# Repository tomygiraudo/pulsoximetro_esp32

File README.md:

# Pulsoximetro portátil WI-FI

Diseño open-source de un pulsioxímetro doméstico portátil con conexión WI-FI para la materia de instrumentación Biomédica, realizado con un ESP32-C3 Super mini, un sensor de Fotoplestimografía (PPG) MAX30102, un circuito de carga y control de batería, una baterpia de 3.7 V y 230 mAh y una pantalla TFT 128x128 px con controlador STF775S.
<div align="center"> 

</div>

Detalles:

- **Ciclo de medición:** el dashboard espera en "Listo para medir" hasta que el
  ESP32 manda el paquete de inicio (se presionó el botón de medición); recién
  entonces aparecen las lecturas, el cronómetro y la traza PPG. Al terminar la
  medición el dashboard deja 2 minutos el resultado final (SpO₂, BPM y la señal)
  antes de volver a "Listo para medir"; si se empieza otra medición antes, la
  reemplaza.
- **Firmware** El firmware se encuentra en firmware/pulsox, tiene integrado todo lo hecho en los distintos tests de las otras carpetas.
- **Credenciales** Para que el pulsoxímetro se conecte a la aplicación y a la base de datos, se debe clonar el codigo de la base de datos y alojarlo en un proyecto firebase local. Por ultimo crear un archivo .env con las credenciales de la red wifi y las API's correspondientes para establecer la conexión con la base de datos.

## Procesamiento de Señal y diseño de filtros en Python
https://colab.research.google.com/drive/18P-XyyEuqM189sJWGMnf9TlH9UD-HeR_?usp=sharing 

Links útiles del fabricante del MAX30102: 
https://www.analog.com/en/resources/reference-designs/maxrefdes117.html
https://www.analog.com/en/resources/technical-articles/how-to-design-a-better-pulse-oximeter.html 
https://www.analog.com/en/resources/technical-articles/guidelines-for-spo2-measurement--maxim-integrated.html
https://www.scielo.cl/scielo.php?script=sci_arttext&pid=S0717-73482010000100010

## Hardware
El esquemático del pulsioxímetro y todos sus componentes necesarios se detallan en PCB/Esquematico_V2.pdf/. Los archivos de diseño de la PCB se encuentran dentro de la misma carpeta. 

## Impresión de Carcasa
Los archivos STL para la impresión de la carcasa se encuentran en Carcasa/. Las partes fueron impresas en PETG para una mayor resistencia. 
**Parámetros de Impresión**
-  Altura de capa: 0,16 mm
-  Perímetros: 5 * 0,4 mm
-  Relleno: 50% o superior

## Telemetría del ESP32

El ESP32-C3 envía cada medición por **HTTPS (REST) a Firebase Realtime Database**. La web app la muestra en vivo y la guarda en el historial.

- **Conexión:** al presionar el botón, el ESP32 se conecta al WiFi, inicia sesión en Firebase y mantiene una sola conexión TLS abierta durante la medición.
- **En vivo (1 Hz):** cada segundo reemplaza `devices/<id>/live` con SpO₂, BPM, calidad de señal, estado del dedo y la traza PPG (50 muestras/s). Al terminar, borra `live`.
- **Historial:** una medición válida (45–60 s) guarda una única lectura final en `sessions/<sid>`. El valor es la mediana de los últimos 20 s válidos. Si la medición se descarta (dedo retirado o señal errática), la sesión se borra.
- **Credenciales:** WiFi, API key y usuario del dispositivo van en `firmware/pulsox/include/secrets.h`. El archivo se crea a partir de `secrets.h.example` y no se sube al repo.

Detalle de nodos, llamadas REST y reglas de seguridad en [`PROTOCOL.md`](PROTOCOL.md). Firmware en [`firmware/pulsox`](firmware/pulsox).

## Sistema de diseño y tipografías para pantalla y app web 

Ver [`design-system/pulsox-esp32/`](design-system/pulsox-esp32/): paleta,
tipografía, formas y especificación de componentes (gauge de SpO2, tarjeta de
frecuencia cardíaca, traza PPG, barra de navegación, historial) usados por la
web app.
<div align="center">
   
</div>
<div align="center">
                        
  </div>

## Próximos pasos

- Comparar mediciones con un patrón y realizar una calibración o informe de resultados.

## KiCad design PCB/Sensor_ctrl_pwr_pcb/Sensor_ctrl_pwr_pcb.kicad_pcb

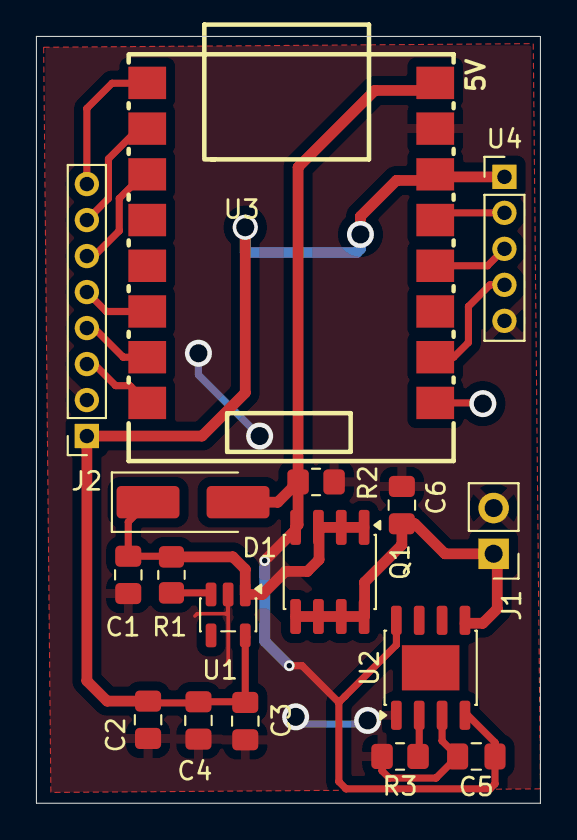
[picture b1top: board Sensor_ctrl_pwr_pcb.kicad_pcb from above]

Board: 2 copper layers, 28.0 x 42.6 mm, 17 parts (0 on the bottom side), 16 nets.

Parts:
C1, C2, C4, C5, C6: 10uF; C_0805_2012Metric_Pad1.18x1.45mm_HandSolder
C3: 1uF; C_0805_2012Metric_Pad1.18x1.45mm_HandSolder
D1: 1N5819; D_SMA_Handsoldering
J1: BATTERY 320 mAh; PinHeader_1x02_P2.54mm_Vertical
J2: TFT SCREEN PINOUT; PinSocket_1x08_P2.00mm_Vertical
Q1: PMOS; SOIC-8_3.9x4.9mm_P1.27mm
R1, R2: 100K; R_0805_2012Metric_Pad1.20x1.40mm_HandSolder
R3: 10K; R_0805_2012Metric_Pad1.20x1.40mm_HandSolder
U1: AP2112K-3.3; SOT-23-5
U2: TP4056-42-ESOP8; SOIC-8-1EP_3.9x4.9mm_P1.27mm_EP2.514x3.2mm
U3: ESP32C3-SUPERMINI; COMM-SMD_16P-L22.5-W18.0-P2.54-TL
U4: module_max30102; PinHeader_1x05_P2.00mm_Vertical

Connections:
+3V3: C2.1, C3.1, C4.1, J2.1, U1.5 (VOUT), U3.14 (3V3), U4.1 (VIN)
/BACKLIGHT_TFT: J2.8, U3.1 (GPIO5)
/CS_TFT: J2.3, U3.8 (GPIO21)
/DATA_SEL_TFT: J2.5, U3.6 (GPIO10)
/EN: R1.2, U1.3 (EN)
/INT-OX: U3.10 (GPIO1), U4.4 (INT)
/RST_TFT: J2.4, U3.7 (GPIO20)
/SCK_TFT: J2.7, U3.2 (GPIO6)
/SCL-OX: U3.13 (GPIO4), U4.2 (SCL)
/SDA-OX: U3.12 (GPIO3), U4.3 (SDA)
/SDA_TFT: J2.6, U3.3 (GPIO7)
GND: C1.2, C2.2, C3.2, C4.2, C5.2, C6.2, J1.2, J2.2, R2.2, R3.2, U1.2 (GND), U2.1 (TEMP), U2.3 (GND), U3.15 (GND), U4.5 (IRD)
unnamed: C1.1, D1.1 (K), Q1.1 (D), Q1.2 (G), Q1.3 (S), R1.1, U1.1 (VIN)
unnamed: R3.1, U2.2 (PROG)
VBAT: C6.1, J1.1, Q1.5, Q1.6, Q1.7, Q1.8, U2.5 (BAT)
VBUS: C5.1, D1.2 (A), Q1.4, R2.1, U2.4 (V_{CC}), U2.8 (CE), U3.16 (5V)

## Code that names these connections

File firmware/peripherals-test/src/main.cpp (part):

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//     the SDA/SCL/INT levels; in live mode one stats line per second.
//
// Pins are the ones in PCB/Sensor_ctrl_pwr_pcb (KiCad schematic, "Esquematico V2"):
//   SDA-OX  GPIO3   I2C SDA (MAX30102)
//   SCL-OX  GPIO4   I2C SCL (MAX30102)
//   INT-OX  GPIO1   MAX30102 INT (open-drain, active low)
//   SCK_TFT GPIO6   SPI clock
//   SDA_TFT GPIO7   SPI MOSI (bidirectional SDA on the ST7735S)
//   CS_TFT  GPIO21  SPI chip select
//   DATA_SEL_TFT GPIO10  D/C (A0)
//   RST_TFT GPIO20  TFT hardware reset
//   BACKLIGHT_TFT GPIO5  TFT backlight (LED pin of the module)
//   SW1     GPIO0   push button (not used by this test)
//
// Live mode also streams "ir:<n>,red:<n>" lines, so the values can be
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#define PIN_SDA_OX 3
#define PIN_SCL_OX 4
#define PIN_INT_OX 1
#define PIN_SCK_TFT 6
#define PIN_SDA_TFT 7
#define PIN_CS_TFT 21
#define PIN_DC_TFT 10
#define PIN_RST_TFT 20
#define PIN_BL_TFT 5

#define BL_ON HIGH   // flip to LOW if the backlight turns out to be active-low
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};

#if TFT_USE_SOFT_SPI
static TftPanel tft(PIN_CS_TFT, PIN_DC_TFT, PIN_SDA_TFT, PIN_SCK_TFT, PIN_RST_TFT);
#else
static TftPanel tft(&SPI, PIN_CS_TFT, PIN_DC_TFT, PIN_RST_TFT);
#endif
static GFXcanvas16 plot(TFT_W, PLOT_H);
#endif
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// with D/C high. SPI mode 0 (idle low, MOSI latched on the rising edge).
static void tftBitWriteByte(uint8_t b) {
  for (uint8_t i = 0; i < 8; i++) {
    digitalWrite(PIN_SCK_TFT, LOW);
    digitalWrite(PIN_SDA_TFT, (b & 0x80) ? HIGH : LOW);
    delayMicroseconds(2);
    digitalWrite(PIN_SCK_TFT, HIGH);
    delayMicroseconds(2);
    b <<= 1;
  }
}

static void tftReadReg(uint8_t cmd, uint8_t *out, uint8_t n) {
  pinMode(PIN_CS_TFT, OUTPUT);
  pinMode(PIN_DC_TFT, OUTPUT);
  pinMode(PIN_SCK_TFT, OUTPUT);
  pinMode(PIN_SDA_TFT, OUTPUT);

  digitalWrite(PIN_SCK_TFT, LOW);
  digitalWrite(PIN_CS_TFT, LOW);
  digitalWrite(PIN_DC_TFT, LOW);
  tftBitWriteByte(cmd);

  digitalWrite(PIN_SCK_TFT, LOW);
  digitalWrite(PIN_DC_TFT, HIGH);
  pinMode(PIN_SDA_TFT, INPUT);

  // dummy clock cycle
  delayMicroseconds(2);
  digitalWrite(PIN_SCK_TFT, HIGH);
  delayMicroseconds(2);
  digitalWrite(PIN_SCK_TFT, LOW);

  for (uint8_t i = 0; i < n; i++) {
    uint8_t v = 0;
    for (uint8_t bit = 0; bit < 8; bit++) {
      delayMicroseconds(2); // data changes on the falling edge, sample before the rising one
      v = (v << 1) | (digitalRead(PIN_SDA_TFT) ? 1 : 0);
      digitalWrite(PIN_SCK_TFT, HIGH);
      delayMicroseconds(2);
      digitalWrite(PIN_SCK_TFT, LOW);
    }
    out[i] = v;
  }

  digitalWrite(PIN_CS_TFT, HIGH);
  pinMode(PIN_SDA_TFT, OUTPUT);
}

static void tftHardwareReset() {
  pinMode(PIN_RST_TFT, OUTPUT);
  digitalWrite(PIN_RST_TFT, HIGH);
  delay(5);
  digitalWrite(PIN_RST_TFT, LOW);
  delay(10);
  digitalWrite(PIN_RST_TFT, HIGH);
  delay(120);
}

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    uint8_t pin;
    const char *name;
  };
  const Line lines[] = {{PIN_CS_TFT, "CS"},   {PIN_DC_TFT, "DC"},   {PIN_RST_TFT, "RST"},
                        {PIN_SCK_TFT, "SCK"}, {PIN_SDA_TFT, "SDA"}, {PIN_BL_TFT, "BL"}};
  const uint8_t n = sizeof(lines) / sizeof(lines[0]);
  bool ok = true;

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  }

  // Leave every line in its idle state.
  digitalWrite(PIN_CS_TFT, HIGH);
  digitalWrite(PIN_DC_TFT, HIGH);
  digitalWrite(PIN_RST_TFT, HIGH);
  digitalWrite(PIN_BL_TFT, BL_ON);
  if (ok) {
    DBG("TFT", "pin check: sin cortos ni puentes entre CS/DC/RST/SCK/SDA/BL "
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  tftReadReg(TFT_CMD_RDDID, tftId, 3);

  DBG("TFT", "initR(): SPI por %s, SCK=GPIO%d SDA=GPIO%d CS=GPIO%d DC=GPIO%d RST=GPIO%d",
      TFT_USE_SOFT_SPI ? "SOFTWARE" : "hardware", PIN_SCK_TFT, PIN_SDA_TFT, PIN_CS_TFT, PIN_DC_TFT,
      PIN_RST_TFT);
#if !TFT_USE_SOFT_SPI
  SPI.begin(PIN_SCK_TFT, -1, PIN_SDA_TFT, -1); // no MISO, no hardware CS
  // (the core logs "SPI Does not have default pins on ESP32C3" for MISO=-1: harmless)
#endif
  tft.initR(TFT_INIT_TAB);
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#endif
  tftReadReg(TFT_CMD_RDDPM, &tftRddpmAfter, 1);
#if !TFT_USE_SOFT_SPI
  SPI.begin(PIN_SCK_TFT, -1, PIN_SDA_TFT, -1);
#endif

  Serial.printf("RDDID  = %02X %02X %02X (ST7735S suele dar 7C 89 F0, los clones varian)\n",
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  uint8_t j2;
  const char *name;
};
static const TftLine TFT_LINES[] = {{PIN_CS_TFT, 3, "CS"},   {PIN_RST_TFT, 4, "RST"},
                                    {PIN_DC_TFT, 5, "A0/DC"}, {PIN_SDA_TFT, 6, "SDA"},
                                    {PIN_SCK_TFT, 7, "SCK"},  {PIN_BL_TFT, 8, "LED"}};
#define TFT_LINE_COUNT ((uint8_t)(sizeof(TFT_LINES) / sizeof(TFT_LINES[0])))

// Mode 1: every line goes to a logic 1 (3.3 V) and stays there.
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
